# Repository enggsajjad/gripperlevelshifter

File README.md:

# gripperlevelshifter

by Sajjad hussain

- BOM: the bom and digikey parts lists.
	-- current digikey part list: https://www.digikey.de/short/rwjj28b7
- pdf: schematic pdfs
- Datasheet: different datasheets
- PCB: the schematic and the PCB

	-- Simple: i.e., only using a optocoupler to shift the level

	-- with relay: capable of driving more current and more secure/isolation

	-- added jumpers to test both the versions

	-- added another version with mosfet with 3 gpios from 3.3v to 24V

## Getting started

To make it easy for you to get started with GitLab, here's a list of recommended next steps.

Already a pro? Just edit this README.md and make it your own. Want to make it easy? [Use the template at the bottom](#editing-this-readme)!

## Add your files

- [ ] [Create](https://docs.gitlab.com/ee/user/project/repository/web_editor.html#create-a-file) or [upload](https://docs.gitlab.com/ee/user/project/repository/web_editor.html#upload-a-file) files
- [ ] [Add files using the command line](https://docs.gitlab.com/ee/gitlab-basics/add-file.html#add-a-file-using-the-command-line) or push an existing Git repository with the following command:

```
cd existing_repo
git remote add origin https://ids-git.fzi.de/xp234/gripperlevelshifter.git
git branch -M main
git push -uf origin main
```

## Integrate with your tools

- [ ] [Set up project integrations](https://ids-git.fzi.de/xp234/gripperlevelshifter/-/settings/integrations)

## Collaborate with your team

- [ ] [Invite team members and collaborators](https://docs.gitlab.com/ee/user/project/members/)
- [ ] [Create a new merge request](https://docs.gitlab.com/ee/user/project/merge_requests/creating_merge_requests.html)
- [ ] [Automatically close issues from merge requests](https://docs.gitlab.com/ee/user/project/issues/managing_issues.html#closing-issues-automatically)
- [ ] [Enable merge request approvals](https://docs.gitlab.com/ee/user/project/merge_requests/approvals/)
- [ ] [Set auto-merge](https://docs.gitlab.com/ee/user/project/merge_requests/merge_when_pipeline_succeeds.html)

## Test and Deploy

Use the built-in continuous integration in GitLab.

- [ ] [Get started with GitLab CI/CD](https://docs.gitlab.com/ee/ci/quick_start/index.html)
- [ ] [Analyze your code for known vulnerabilities with Static Application Security Testing (SAST)](https://docs.gitlab.com/ee/user/application_security/sast/)
- [ ] [Deploy to Kubernetes, Amazon EC2, or Amazon ECS using Auto Deploy](https://docs.gitlab.com/ee/topics/autodevops/requirements.html)
- [ ] [Use pull-based deployments for improved Kubernetes management](https://docs.gitlab.com/ee/user/clusters/agent/)
- [ ] [Set up protected environments](https://docs.gitlab.com/ee/ci/environments/protected_environments.html)

***

# Editing this README

When you're ready to make this README your own, just edit this file and use the handy template below (or feel free to structure it however you want - this is just a starting point!). Thanks to [makeareadme.com](https://www.makeareadme.com/) for this template.

## Suggestions for a good README

Every project is different, so consider which of these sections apply to yours. The sections used in the template are suggestions for most open source projects. Also keep in mind that while a README can be too long and detailed, too long is better than too short. If you think your README is too long, consider utilizing another form of documentation rather than cutting out information.

## Name
Choose a self-explaining name for your project.

## Description
Let people know what your project can do specifically. Provide context and add a link to any reference visitors might be unfamiliar with. A list of Features or a Background subsection can also be added here. If there are alternatives to your project, this is a good place to list differentiating factors.

## Badges
On some READMEs, you may see small images that convey metadata, such as whether or not all the tests are passing for the project. You can use Shields to add some to your README. Many services also have instructions for adding a badge.

## Visuals
Depending on what you are making, it can be a good idea to include screenshots or even a video (you'll frequently see GIFs rather than actual videos). Tools like ttygif can help, but check out Asciinema for a more sophisticated method.

## Installation
Within a particular ecosystem, there may be a common way of installing things, such as using Yarn, NuGet, or Homebrew. However, consider the possibility that whoever is reading your README is a novice and would like more guidance. Listing specific steps helps remove ambiguity and gets people to using your project as quickly as possible. If it only runs in a specific context like a particular programming language version or operating system or has dependencies that have to be installed manually, also add a Requirements subsection.

## Usage
Use examples liberally, and show the expected output if you can. It's helpful to have inline the smallest example of usage that you can demonstrate, while providing links to more sophisticated examples if they are too long to reasonably include in the README.

## Support
Tell people where they can go to for help. It can be any combination of an issue tracker, a chat room, an email address, etc.

## Roadmap
If you have ideas for releases in the future, it is a good idea to list them in the README.

## Contributing
State if you are open to contributions and what your requirements are for accepting them.

For people who want to make changes to your project, it's helpful to have some documentation on how to get started. Perhaps there is a script that they should run or some environment variables that they need to set. Make these steps explicit. These instructions could also be useful to your future self.

You can also document commands to lint the code or run tests. These steps help to ensure high code quality and reduce the likelihood that the changes inadvertently break something. Having instructions for running tests is especially helpful if it requires external setup, such as starting a Selenium server for testing in a browser.

## Authors and acknowledgment
Show your appreciation to those who have contributed to the project.

## License
For open source projects, say how it is licensed.

## Project status
If you have run out of energy or time for your project, put a note at the top of the README saying that development has slowed down or stopped completely. Someone may choose to fork your project or volunteer to step in as a maintainer or owner, allowing your project to keep going. You can also make an explicit request for maintainers.

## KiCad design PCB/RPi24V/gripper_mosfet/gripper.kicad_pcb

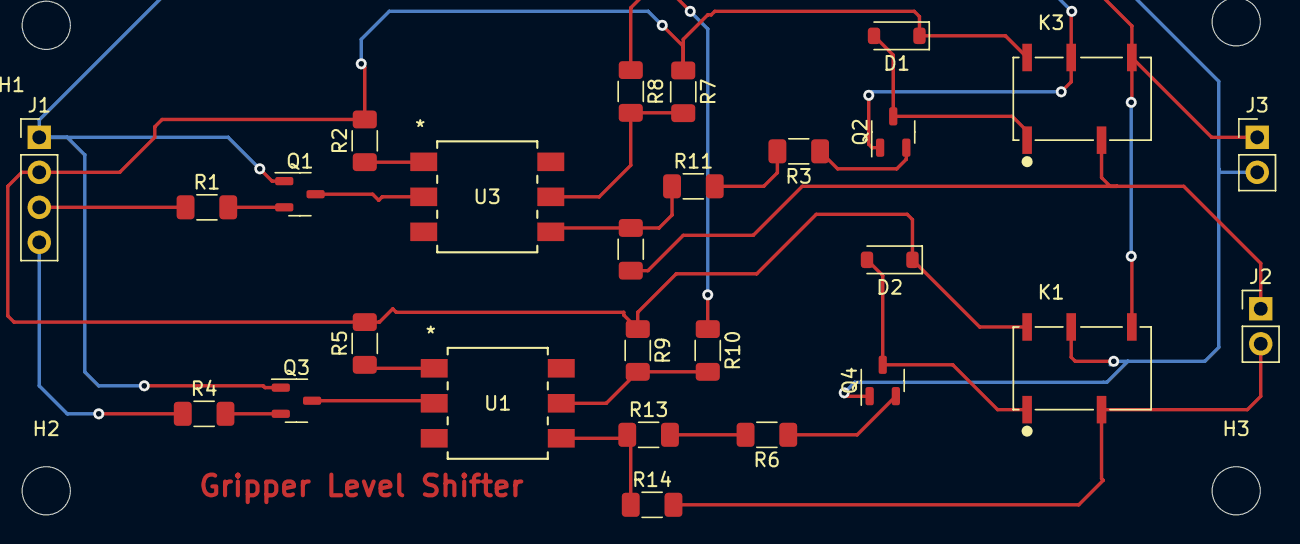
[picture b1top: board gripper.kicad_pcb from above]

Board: 2 copper layers, 31 parts (0 on the bottom side), 23 nets.

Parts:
D1, D2: 1N4148; D_SOD-123
H1, H2, H3, H4: MountingHole; MountingHole_3.5mm
J1: Conn_01x04_Pin; PinHeader_1x04_P2.54mm_Vertical
J2, J3: Conn_01x02_Pin; PinHeader_1x02_P2.54mm_Vertical
K1, K3: 1462042-8; RELAY_1462042-8
Q1, Q2, Q3, Q4: PN2222A; SOT-23-3
R1, R4: 10K; R_1206_3216Metric_Pad1.30x1.75mm_HandSolder
R2, R5: 200R; R_1206_3216Metric_Pad1.30x1.75mm_HandSolder
R3, R6: 5.1K; R_1206_3216Metric_Pad1.30x1.75mm_HandSolder
R7, R8, R9, R10, R11, R12, R13, R14: 0R; R_1206_3216Metric_Pad1.30x1.75mm_HandSolder
U1, U3: 4N35S-TA1; SO6_4N35S_LTO

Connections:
+5V: D1.1 (K), D2.1 (K), J1.2, K1.8, K3.8, R2.2, R5.2, R7.1, R9.1
+24V: J3.1, K1.5, K3.5, R8.1, R10.1
GND: J1.1, J3.2, K1.7, K3.7, Q1.1 (E), Q2.1 (E), Q3.1 (E), Q4.1 (E)
GPIO1: J1.3, R1.1
GPIO1_24: J2.1, K3.3, R12.2
GPIO2: J1.4, R4.1
GPIO2_24: J2.2, K1.3, R14.2
unnamed: D1.2 (A), K3.1, Q2.3 (C)
unnamed: D2.2 (A), K1.1, Q4.3 (C)
unnamed: Q1.2 (B), R1.2
unnamed: Q1.3 (C), U3.2
unnamed: Q2.2 (B), R3.1
unnamed: Q3.2 (B), R4.2
unnamed: Q3.3 (C), U1.2
unnamed: Q4.2 (B), R6.1
unnamed: R2.1, U3.1
unnamed: R5.1, U1.1
unnamed: R7.2, R8.2, U3.5
unnamed: R9.2, R10.2, U1.5
unnamed: R11.1, R12.1, U3.4
unnamed: R3.2, R11.2
unnamed: R13.1, R14.1, U1.4
unnamed: R6.2, R13.2

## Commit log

2023-12-21 committing the final from fzi
